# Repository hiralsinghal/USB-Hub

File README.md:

# USB-Hub

This is a USB hub. It has a USB-C port to connect to the device. It has two USB-A ports and two USB-C ports, which can be used for connecting more devices as it allows you to increase the number of ports available.

## Features

- USB-C port to form the connection between the hub and your device.
- 2 USB-A ports
- 2 USB-C ports

## Schematic

This is the schematic for the USB hub. It has an IC, which makes the hub work. 

### Upstream Port

### Integrated Circuit

### Downstream Ports

#### USB-A

#### USB-C

## PCB

Its just a rounded rectangle shaped PCB and has three mounting holes, so it can be screwed into the case.
I added some quotes as silkscreen art.

**No zones**

## Case

I designed this in Fusion, using my PCB as a guide. It has holes for M3 screws so the bottom and top parts hold together. You can find the files in the CAD folder.

## BOM

For a more detailed BOM, take a look at [BOM](bom.csv). It has links to the items and notes.

| Item | Description | Quantity | Unit Price ($) | Total Price ($) |
| --- | --- | --- | --- | --- |
| JLCPCB PCB | PCB | 5 | 0.8 | 4 |
| CoreChips SL2.1s | USB 2.0 HUB Controller Integrated Circuit | 5 | 0.2534 | 1.27 |
| SHOU HAN 10.0 QHHTZB6.3 | CONN RCPT USB 2.0 Type-A 4POS SMD R/A | 10 | 0.0636 | 0.64 |
| SHOU HAN TYPE-C 16PIN 2MD(073) | CONN RCPT Type-C 16POS SMD R/A | 20 | 0.0707 | 1.41 |
| ElecSuper USBLC6-2SC6-ES | ESD DIODE 5VWM 15VC SOT-23-6L | 20 | 0.0278 | 0.56 |
| 10k Resistor SMD:R 0402 | Resistor | 6 | 0.0083 | 0.0498 |
| 0.1uf Capacitor SMD:C 0402 | Capacitor | 11 | 0.011 | 0.121 |
| <b>Total</b> | | | | 8.0508 |

## Assembly

- Solder the components to the PCB.
- Print the case.
- Screw the PCB and the bottom case together so its stable.
- Screw the bottom and top case together.
- You have your USB hub!

## Zine

This was designed in Figma. It wasn't easy to make. I had no ideas. I was stuck. Its not my best work.

## Why did I make it?

I have been trying to get more into hardware, making guided projets before jumping in to make something my own.
I want to have knowledge on how to do this stuff, so I know how to make my own project.
My routing skills were improved. I made them neatly.

This project was submitted to [Fallout](fallout.hackclub.com).

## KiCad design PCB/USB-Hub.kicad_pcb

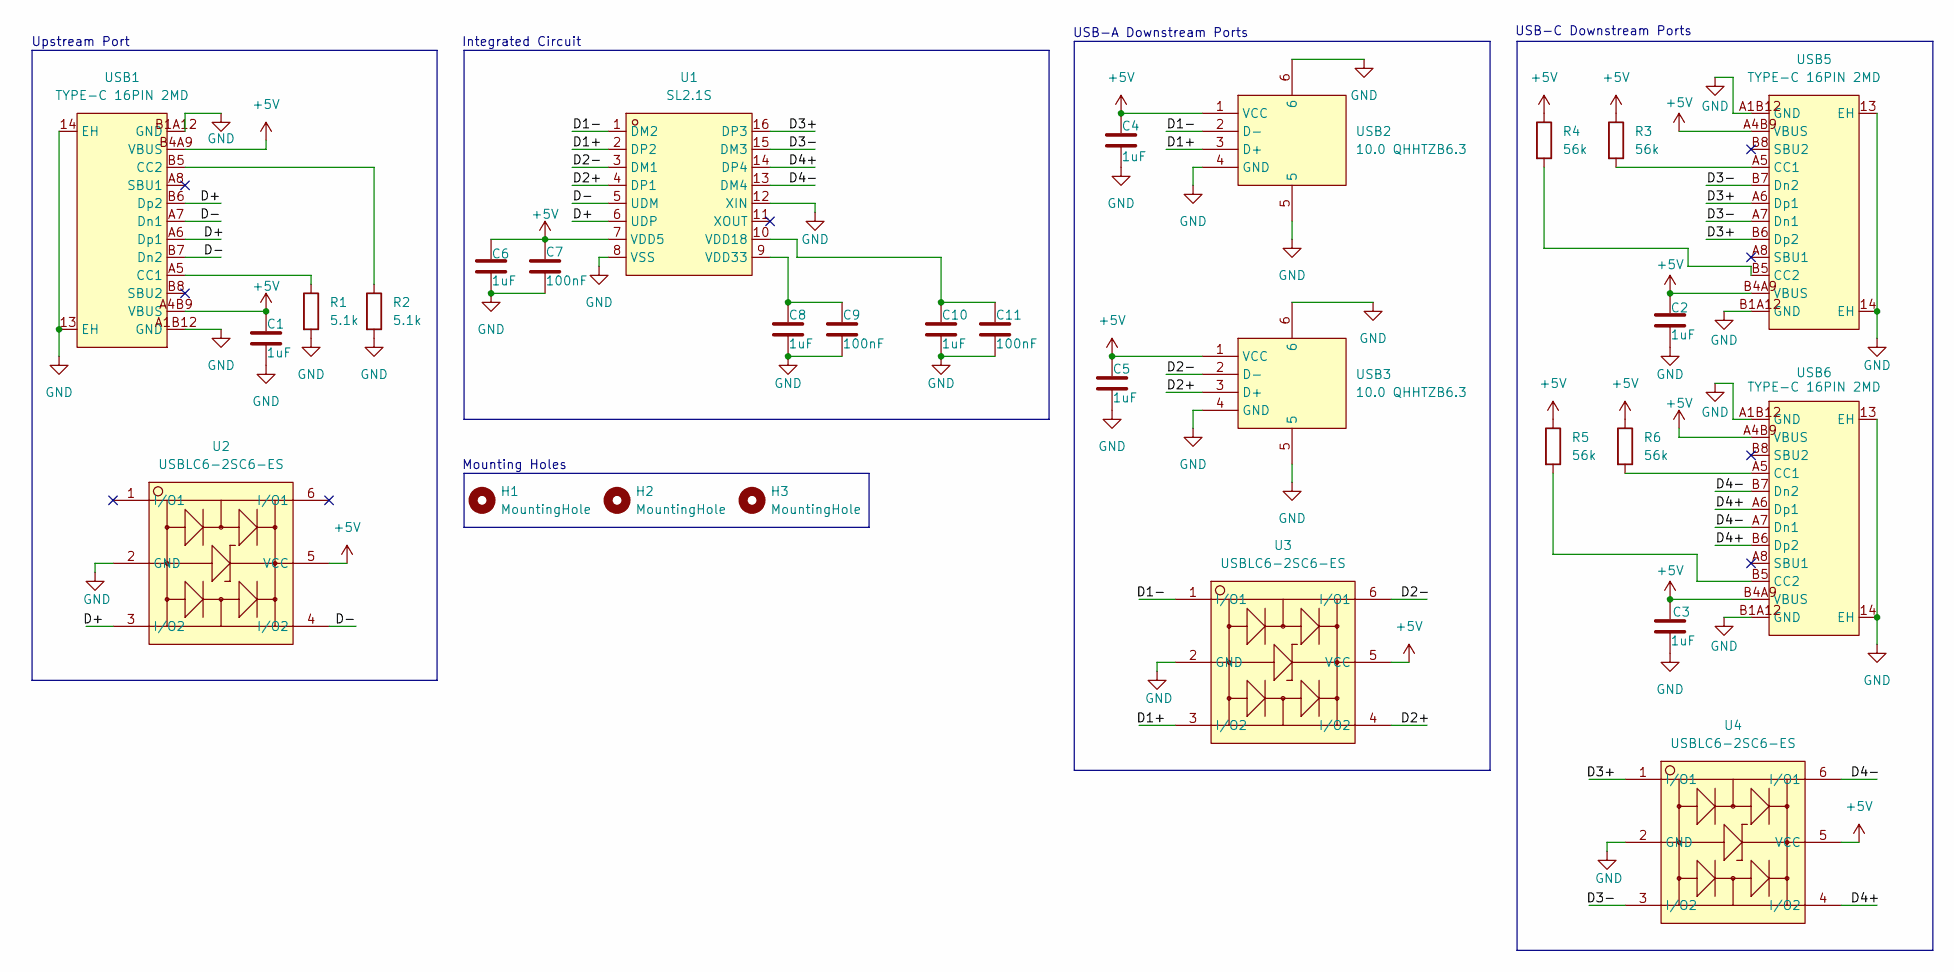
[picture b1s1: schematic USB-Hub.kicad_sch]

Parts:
C1, C2, C3, C4, C5, C6, C8, C10: 1uF; CAPC1005X55N
C7, C9, C11: 100nF; CAPC1005X55N
H1, H2, H3: MountingHole; MountingHole_2.2mm_M2
R1, R2: 5.1k; CAPC1005X60
R3, R4, R5, R6: 56k; CAPC1005X60
U1: SL2.1S; SSOP-16_L4.6-W2.6-P0.53-LS4.0-BL; MPN SL2.1s; LCSC Part C2684433
U2, U3, U4: USBLC6-2SC6-ES; SOT-23-6_L2.9-W1.6-P0.95-LS2.8-BR; MPN USBLC6-2SC6-ES; LCSC Part C5180249
USB1, USB5, USB6: TYPE-C 16PIN 2MD; USB-C-SMD_TYPE-C-16PIN-2MD-073; MPN TYPE-C 16PIN 2MD(073); LCSC Part C2765186
USB2, USB3: 10.0 QHHTZB6.3; USB-A-TH_10.0QHHTZB6.3; MPN 10.0 QHHTZB6.3; LCSC Part C668591

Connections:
+5V: C1.1, C2.1, C3.1, C4.1, C5.1, C6.1, C7.1, R3.1, R4.1, R5.1, R6.1, U1.7 (VDD5), U2.5 (VCC), U3.5 (VCC), U4.5 (VCC), USB1.A4B9 (VBUS), USB1.B4A9 (VBUS), USB2.1 (VCC), USB3.1 (VCC), USB5.A4B9 (VBUS), USB5.B4A9 (VBUS), USB6.A4B9 (VBUS), USB6.B4A9 (VBUS)
/D1+: U1.2 (DP2), U3.3 (I/O2), USB2.3 (D+)
/D1-: U1.1 (DM2), U3.1 (I/O1), USB2.2 (D-)
/D2+: U1.4 (DP1), U3.4 (I/O2), USB3.3 (D+)
/D2-: U1.3 (DM1), U3.6 (I/O1), USB3.2 (D-)
/D3+: U1.16 (DP3), U4.1 (I/O1), USB5.A6 (Dp1), USB5.B6 (Dp2)
/D3-: U1.15 (DM3), U4.3 (I/O2), USB5.A7 (Dn1), USB5.B7 (Dn2)
/D4+: U1.14 (DP4), U4.4 (I/O2), USB6.A6 (Dp1), USB6.B6 (Dp2)
/D4-: U1.13 (DM4), U4.6 (I/O1), USB6.A7 (Dn1), USB6.B7 (Dn2)
/D+: U1.6 (UDP), U2.3 (I/O2), USB1.A6 (Dp1), USB1.B6 (Dp2)
/D-: U1.5 (UDM), U2.4 (I/O2), USB1.A7 (Dn1), USB1.B7 (Dn2)
GND: C1.2, C2.2, C3.2, C4.2, C5.2, C6.2, C7.2, C8.2, C9.2, C10.2, C11.2, R1.2, R2.2, U1.8 (VSS), U1.12 (XIN), U2.2 (GND), U3.2 (GND), U4.2 (GND), USB1.13 (EH), USB1.14 (EH), USB1.A1B12 (GND), USB1.B1A12 (GND), USB2.4 (GND), USB2.5, USB2.6, USB3.4 (GND), USB3.5, USB3.6, USB5.13 (EH), USB5.14 (EH), USB5.A1B12 (GND), USB5.B1A12 (GND), USB6.13 (EH), USB6.14 (EH), USB6.A1B12 (GND), USB6.B1A12 (GND)
unnamed: C10.1, C11.1, U1.10 (VDD18)
unnamed: C8.1, C9.1, U1.9 (VDD33)
unnamed: R1.1, USB1.A5 (CC1)
unnamed: R2.1, USB1.B5 (CC2)
unnamed: R3.2, USB5.A5 (CC1)
unnamed: R4.2, USB5.B5 (CC2)
unnamed: R6.2, USB6.A5 (CC1)
unnamed: R5.2, USB6.B5 (CC2)

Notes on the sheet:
USB-C Downstream Ports
Upstream Port
Mounting Holes
USB-A Downstream Ports
Integrated Circuit

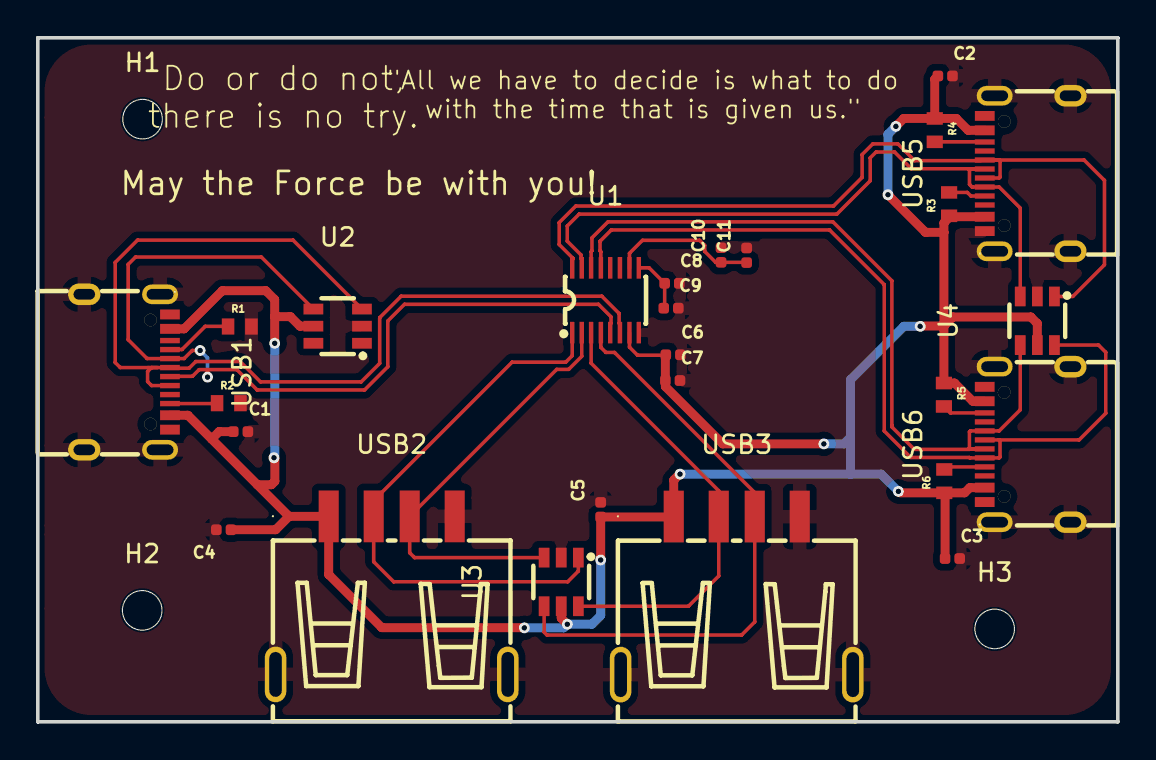
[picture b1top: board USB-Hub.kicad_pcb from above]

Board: 2 copper layers, 60.0 x 38.0 mm, 29 parts (0 on the bottom side), 20 nets.

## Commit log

2026-06-17 readme, pcb folder, bom
2026-06-18 bom and readme
2026-06-18 bom update
2026-06-18 cad stuff
2026-06-19 readme, zine
2026-06-26 update bom,readme
2026-06-26 update pcb
2026-06-26 remove old files
2026-06-26 update gerbers
2026-06-26 update pcb files
2026-06-26 remove files
2026-06-26 remove
2026-06-26 cad and bom update
2026-06-26 remove the filess aahh
2026-06-26 add the newest cad files finally
